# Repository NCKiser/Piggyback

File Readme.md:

Piggyback is a small circuit board that carries an Atmega-32u4-MU microprocessor and all of the supporting components needed for it to run. The only thing you need to provide is 5V power and ground.

Piggyback has 4 legs, each with 8 castellated holes spaced 0.1in (2.54mm) apart. These legs break out all of the GPIO, power, and USB Data pins. Each leg roughly corresponds to a port of the 32u4's IO.

Piggyback was designed with custom mechanical keyboard PCBs in mind. The board fits snuggly under a row of MX or Alps style switches spaced 0.75in (19.05mm) apart. The legs fit within the space between the switch footprints.

Piggyback features ESD protection on the USB data lines, as well as a 500mA resettable polyfuse on the 5V line.

To use the Piggyback in your PCB designs, (load and place the symbol and footprint in your schematic and PCB), and wire it up to your USB port and key matrix. If you are using a USB-C connector, you will need to take care of the CC pins on your own (usually with 5.1k resistors to ground).

PiggybackBT is based on the Kikoto bluetooth pro-micro board, source for that can be found here: https://github.com/zhiayang/mikoto

This is open-source, as long as you give credit, and is free for commercial use. You can make, modify, and sell this board as you please, as long as you do not claim to own the copyright.

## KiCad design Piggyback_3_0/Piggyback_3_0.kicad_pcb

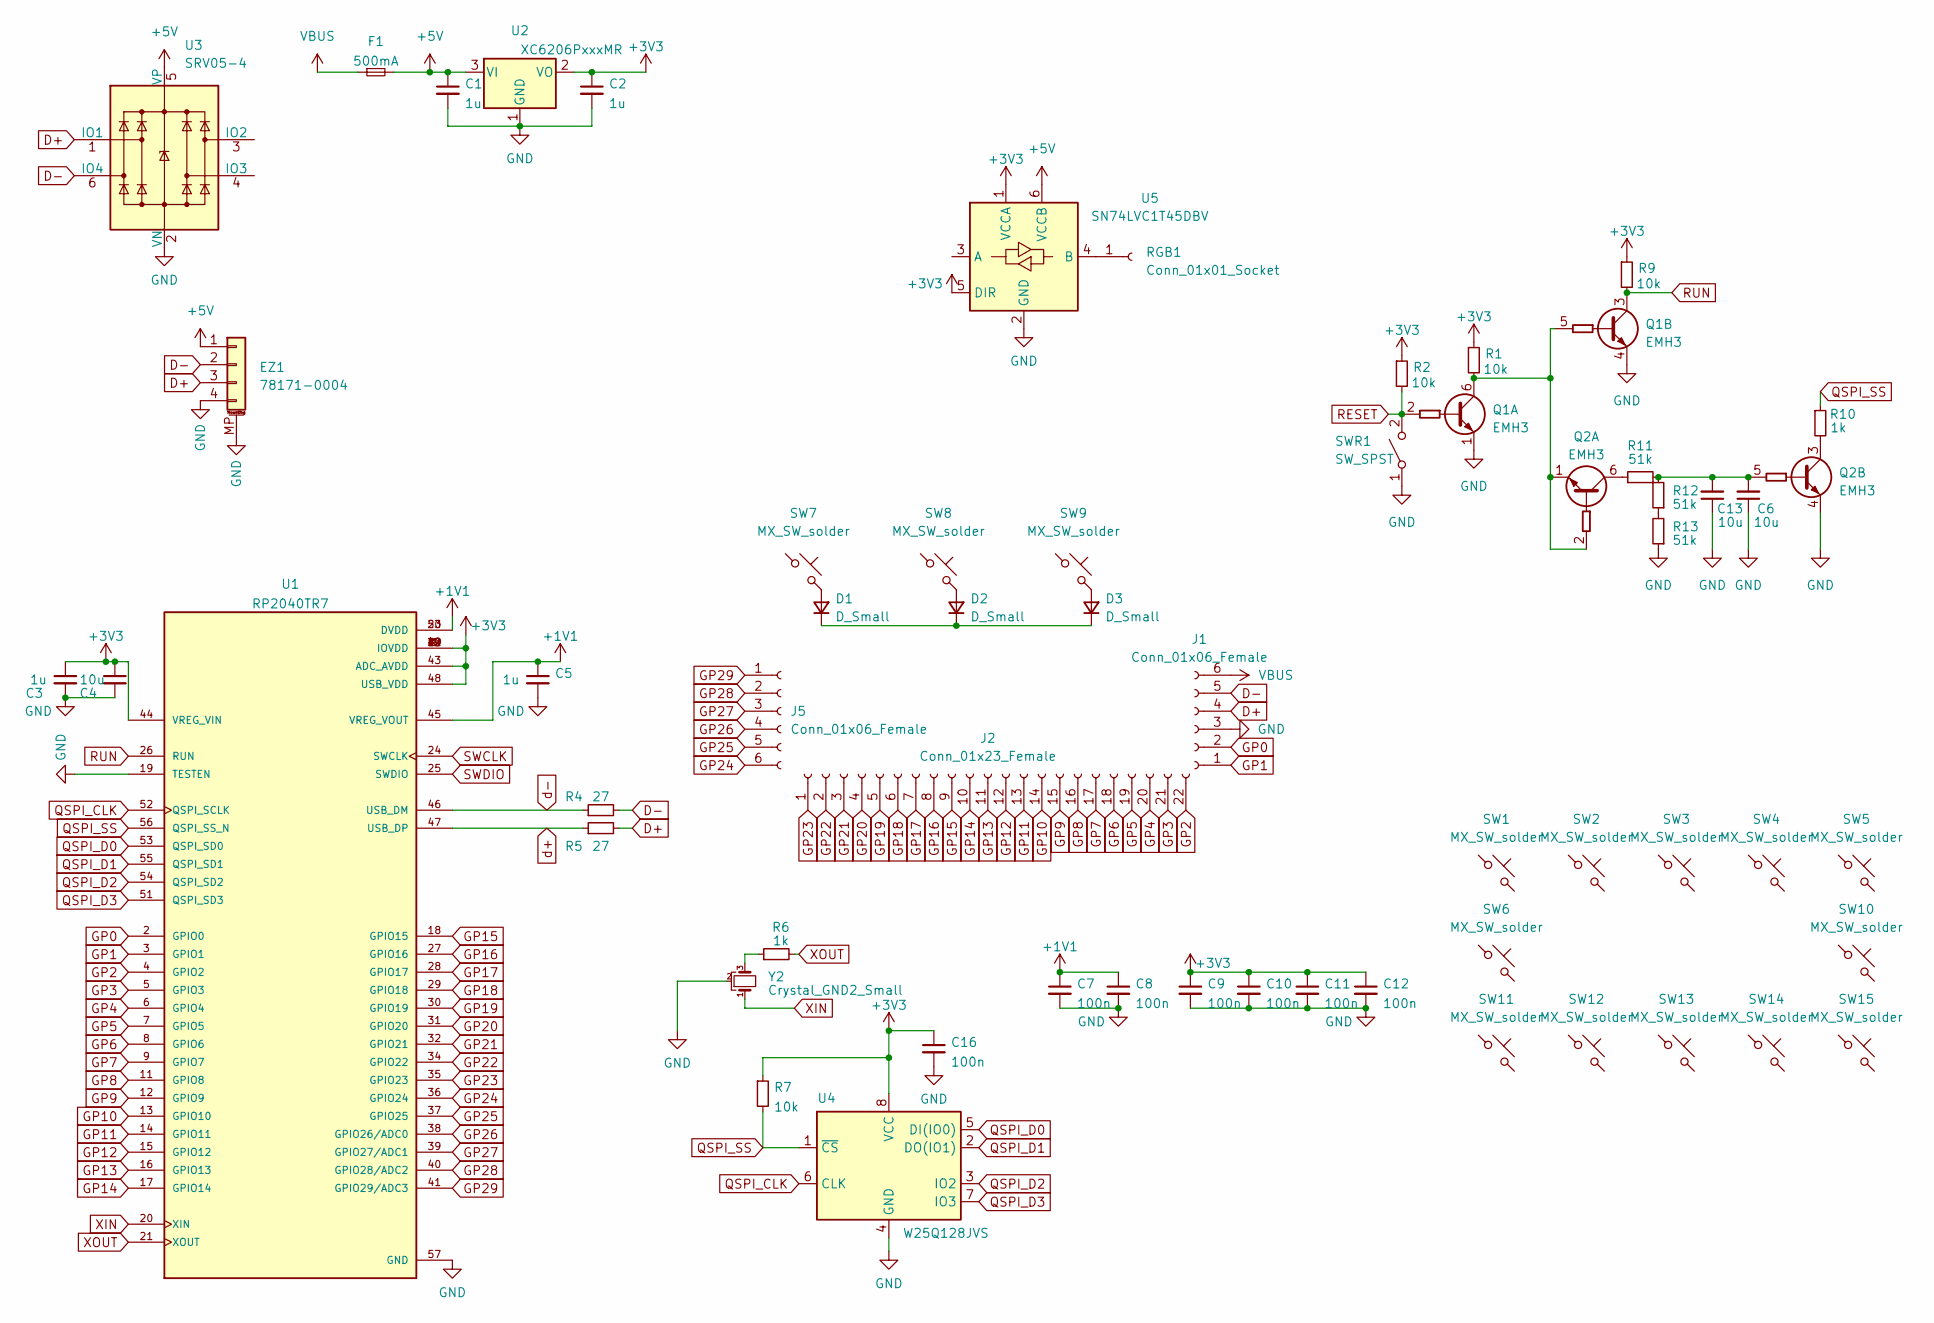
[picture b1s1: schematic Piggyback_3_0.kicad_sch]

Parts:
C1, C2, C3, C5: 1u; C_0402_1005Metric
C4, C6, C13: 10u; C_0402_1005Metric
C7, C8, C9, C10, C11, C12, C16: 100n; C_0402_1005Metric
D1, D2, D3: D_Small; D_SOD-123
EZ1: 78171-0004; PicoEZMate-Reinforced-Lite; Manufacturer Part Number 78171-0004; LCSC Part Number C588524
F1: 500mA; Fuse_1206_3216Metric
J1, J5: Conn_01x06_Female; PinHeader_1x06_P2.54mm_Vertical
J2: Conn_01x23_Female; PinHeader_1x22_P2.54mm_Vertical
Q1, Q2: EMH3; SOT-563
R1, R2, R7, R9: 10k; R_0402_1005Metric
R4, R5: 27; R_0402_1005Metric
R6, R10: 1k; R_0402_1005Metric
R11, R12, R13: 51k; R_0402_1005Metric
RGB1: Conn_01x01_Socket; PinSocket_1x01_P2.54mm_Vertical
SW1, SW2, SW3, SW4, SW5, SW6, SW7, SW8, SW9, SW10, SW11, SW12, SW13, SW14, SW15: MX_SW_solder; SW_MX_1u
SWR1: SW_SPST; SW_Push_SPST_NO_Alps_SKRK
U1: RP2040TR7; QFN40P700X700X90-57N; PARTREV 1.7.1
U2: XC6206PxxxMR; SOT-23
U3: SRV05-4; SOT-23-6-routable
U4: W25Q128JVS; SOIC-8_5.23x5.23mm_P1.27mm
U5: SN74LVC1T45DBV; SOT-23-6
Y2: Crystal_GND2_Small; Resonator_SMD_Murata_CSTxExxV-3Pin_3.0x1.1mm

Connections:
+1V1: C5.1, C7.1, C8.1, U1.23 (DVDD), U1.45 (VREG_VOUT), U1.50 (DVDD)
+3V3: C2.1, C3.1, C4.1, C9.1, C10.1, C11.1, C12.1, C16.1, R1.1, R2.1, R7.1, R9.1, U1.1 (IOVDD), U1.10 (IOVDD), U1.22 (IOVDD), U1.33 (IOVDD), U1.42 (IOVDD), U1.43 (ADC_AVDD), U1.44 (VREG_VIN), U1.48 (USB_VDD), U1.49 (IOVDD), U2.2 (VO), U4.8 (VCC), U5.1 (VCCA), U5.5 (DIR)
+5V: C1.1, EZ1.1, F1.2, U2.3 (VI), U3.5 (VP), U5.6 (VCCB)
D+: EZ1.3, J1.4, R5.2, U3.1 (IO1)
D-: EZ1.2, J1.5, R4.2, U3.6 (IO4)
GND: C1.2, C2.2, C3.2, C4.2, C5.2, C6.1, C7.2, C8.2, C9.2, C10.2, C11.2, C12.2, C13.1, C16.2, EZ1.4, EZ1.MP (MountPin), J1.3, Q1.1 (E1), Q1.4 (E2), Q2.4 (E2), R13.1, SWR1.1 (A), U1.19 (TESTEN), U1.57 (GND), U2.1 (GND), U3.2 (VN), U4.4 (GND), U5.2 (GND), Y2.2
GP0: J1.2, U1.2 (GPIO0)
GP1: J1.1, U1.3 (GPIO1)
GP2: J2.22, U1.4 (GPIO2)
GP3: J2.21, U1.5 (GPIO3)
GP4: J2.20, U1.6 (GPIO4)
GP5: J2.19, U1.7 (GPIO5)
GP6: J2.18, U1.8 (GPIO6)
GP7: J2.17, U1.9 (GPIO7)
GP8: J2.16, U1.11 (GPIO8)
GP9: J2.15, U1.12 (GPIO9)
GP10: J2.14, U1.13 (GPIO10)
GP11: J2.13, U1.14 (GPIO11)
GP12: J2.12, U1.15 (GPIO12)
GP13: J2.11, U1.16 (GPIO13)
GP14: J2.10, U1.17 (GPIO14)
GP15: J2.9, U1.18 (GPIO15)
GP16: J2.8, U1.27 (GPIO16)
GP17: J2.7, U1.28 (GPIO17)
GP18: J2.6, U1.29 (GPIO18)
GP19: J2.5, U1.30 (GPIO19)
GP20: J2.4, U1.31 (GPIO20)
GP21: J2.3, U1.32 (GPIO21)
GP22: J2.2, U1.34 (GPIO22)
GP23: J2.1, U1.35 (GPIO23)
GP24: J5.6, U1.36 (GPIO24)
GP25: J5.5, U1.37 (GPIO25)
GP26: J5.4, U1.38 (GPIO26/ADC0)
GP27: J5.3, U1.39 (GPIO27/ADC1)
GP28: J5.2, U1.40 (GPIO28/ADC2)
GP29: J5.1, U1.41 (GPIO29/ADC3)
unnamed: D1.2 (A), SW7.2
unnamed: D1.1 (K), D2.1 (K), D3.1 (K)
unnamed: D2.2 (A), SW8.2
unnamed: D3.2 (A), SW9.2
unnamed: Q1.5 (B2), Q1.6 (C1), Q2.1 (E1), Q2.2 (B1), R1.2
unnamed: Q2.6 (C1), R11.1
unnamed: C6.2, C13.2, Q2.5 (B2), R11.2, R12.2
unnamed: Q2.3 (C2), R10.2
unnamed: R6.1, Y2.3
unnamed: R12.1, R13.2
unnamed: RGB1.1, U5.4 (B)
QSPI_CLK: U1.52 (QSPI_SCLK), U4.6 (CLK)
QSPI_D0: U1.53 (QSPI_SD0), U4.5 (DI(IO0))
QSPI_D1: U1.55 (QSPI_SD1), U4.2 (DO(IO1))
QSPI_D2: U1.54 (QSPI_SD2), U4.3 (IO2)
QSPI_D3: U1.51 (QSPI_SD3), U4.7 (IO3)
QSPI_SS: R7.2, R10.1, U1.56 (QSPI_SS_N), U4.1 (~CS)
RESET: Q1.2 (B1), R2.2, SWR1.2 (B)
RUN: Q1.3 (C2), R9.2, U1.26 (RUN)
SWCLK: U1.24 (SWCLK)
SWDIO: U1.25 (SWDIO)
VBUS: F1.1, J1.6
XIN: U1.20 (XIN), Y2.1
XOUT: R6.2, U1.21 (XOUT)
d+: R5.1, U1.47 (USB_DP)
d-: R4.1, U1.46 (USB_DM)

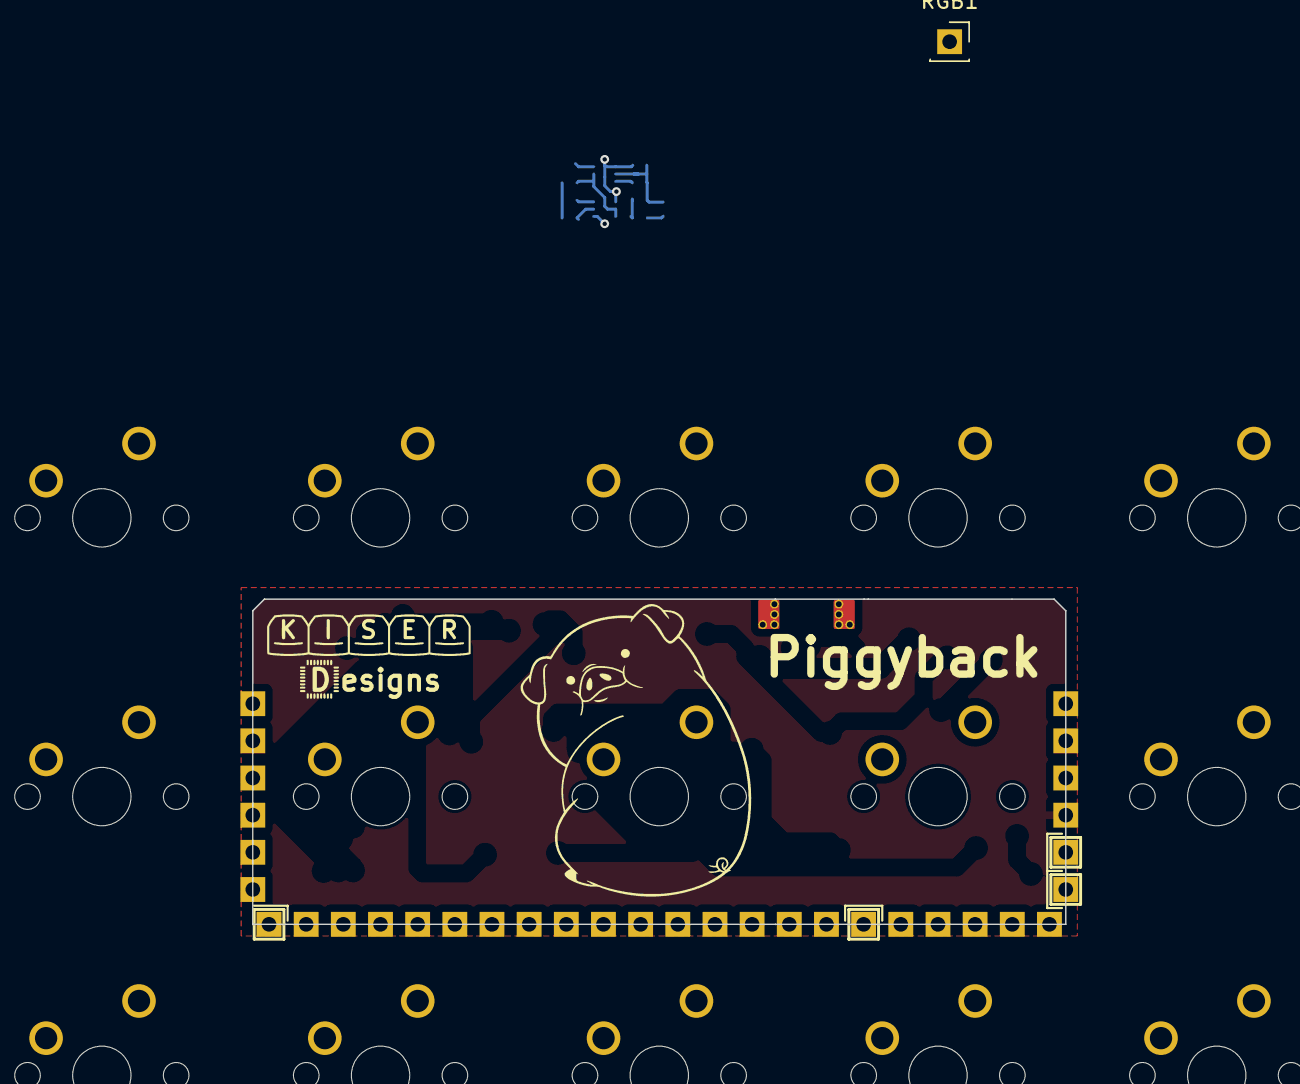
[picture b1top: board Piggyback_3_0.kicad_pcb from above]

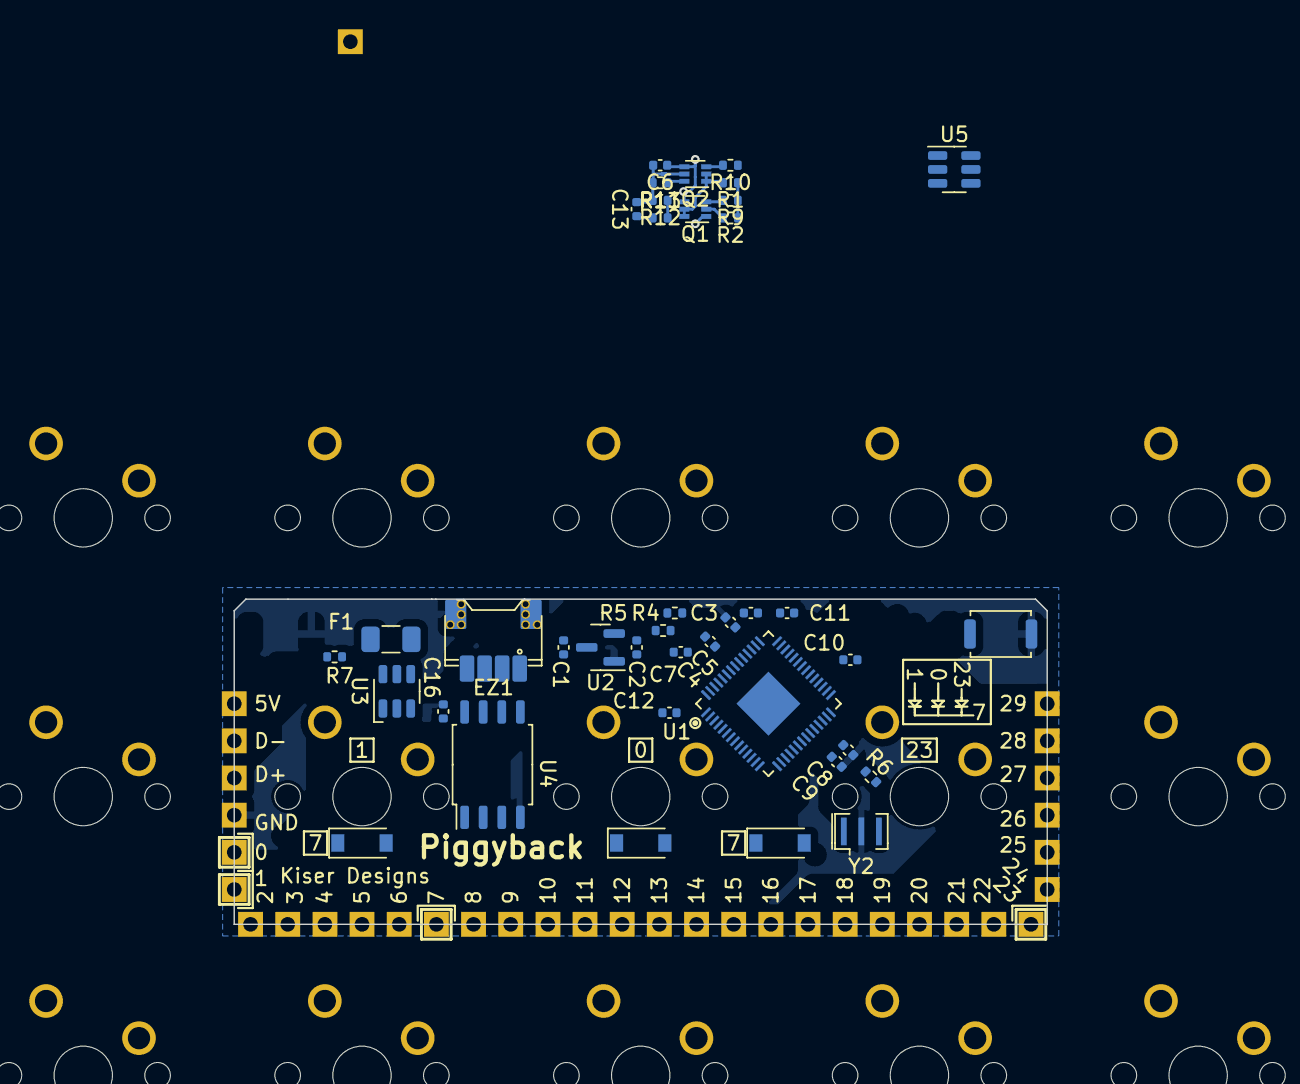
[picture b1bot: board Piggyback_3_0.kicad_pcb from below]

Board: 2 copper layers, 55.6 x 22.2 mm, 58 parts (40 on the bottom side), 60 nets.

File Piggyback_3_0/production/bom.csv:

Designator,Footprint,Quantity,Value,LCSC Part #
"C1, C2, C3, C5",0402,4,1u,
"C10, C11, C12, C16, C7, C8, C9",0402,7,100n,
C4,0402,1,10u,
"D1, D2, D3",D_SOD-123,3,D_Small,
EZ1,PicoEZMate-Reinforced-Lite,1,78171-0004,
F1,1206,1,500mA,
"J1, J5",PinHeader_1x06_P2.54mm_Vertical,2,Conn_01x06_Female,
J2,PinHeader_1x22_P2.54mm_Vertical,1,Conn_01x23_Female,
J3,USB_C_Receptacle_HRO_TYPE-C-31-M-12,1,USB_C_Receptacle_USB2.0,
"R1, R2, R3",0402,3,5.1k,
"R4, R5",0402,2,27,
"R6, R8",0402,2,1k,
R7,0402,1,-10k,
"SW7, SW8, SW9",SW_MX_1u,3,MX_SW_solder,
"SWR1, SWR2",SW_Push_SPST_NO_Alps_SKRK,2,SW_SPST,
U1,QFN40P700X700X90-57N,1,RP2040TR7,
U2,SOT-23,1,XC6206PxxxMR,
U3,SOT-23-6-routable,1,SRV05-4,
U4,SOIC-8_5.23x5.23mm_P1.27mm,1,W25Q128JVS,
Y2,Resonator_SMD_Murata_CSTxExxV-3Pin_3.0x1.1mm,1,Crystal_GND2_Small,

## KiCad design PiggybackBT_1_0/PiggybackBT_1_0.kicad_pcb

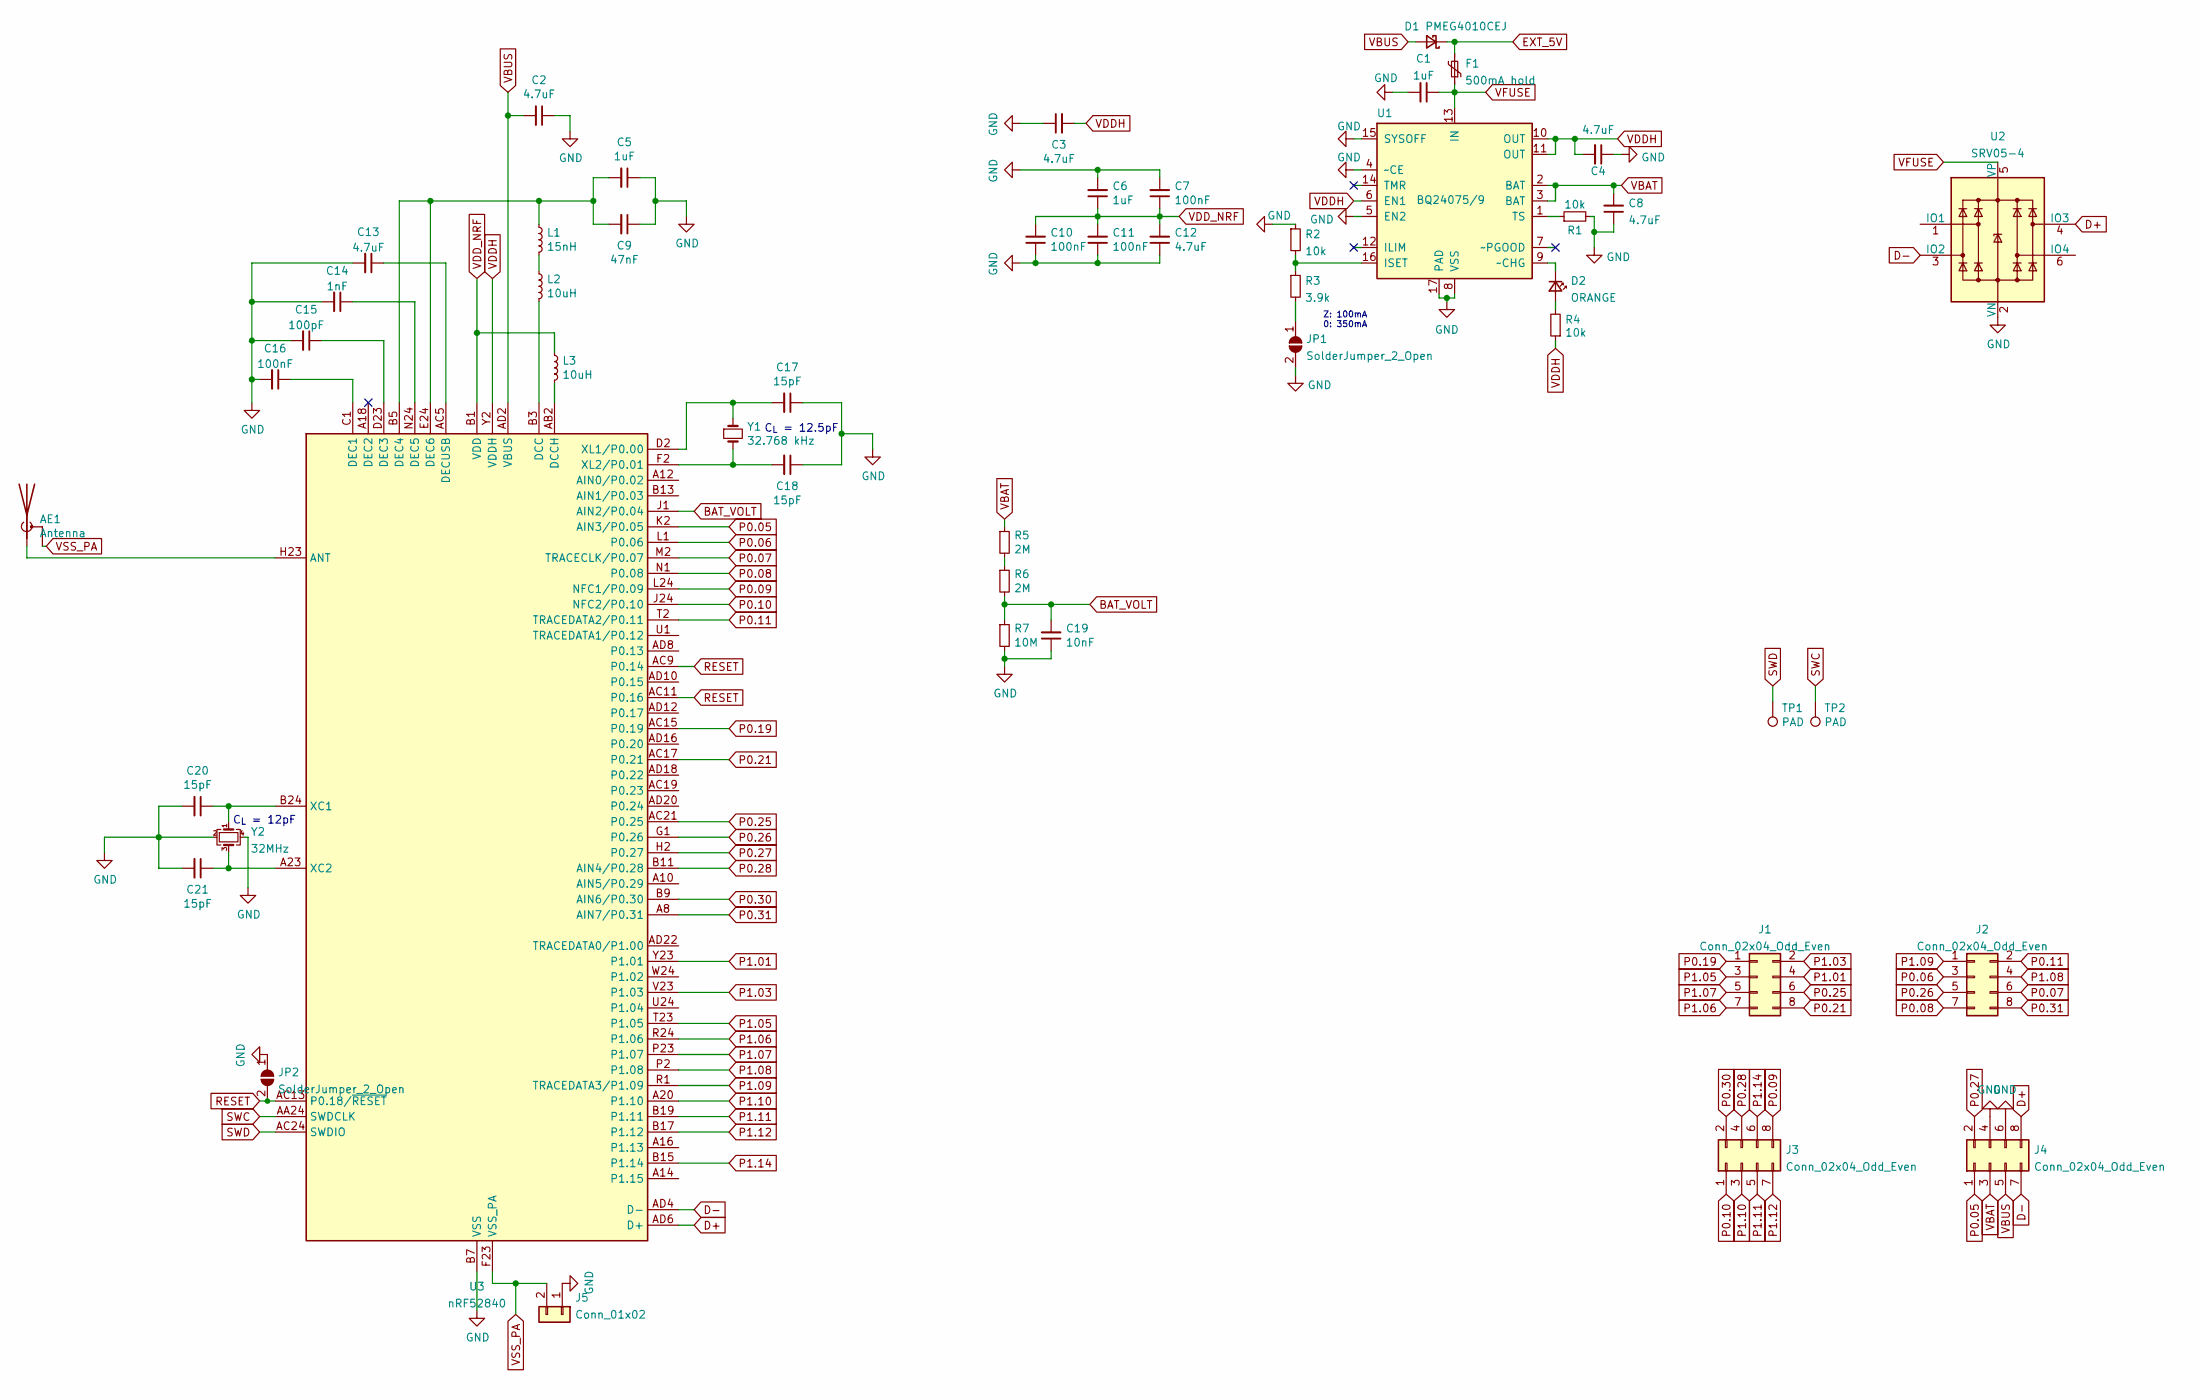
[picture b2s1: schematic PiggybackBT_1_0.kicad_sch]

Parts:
AE1: Antenna; U.FL_Hirose_U.FL-R-SMT-1_Vertical
C1, C5, C6: 1uF; C_0402_1005Metric; Manufacturer Part CL05A105KO5NNNC; LCSC Part C52923
C2, C3, C4, C8, C12, C13: 4.7uF; C_0402_1005Metric; Manufacturer Part CL05A475KP5NRNC; LCSC Part C368809
C7, C10, C11, C16: 100nF; C_0402_1005Metric; Manufacturer Part CL05B104KA5NNNC; LCSC Part C1525
C9: 47nF; C_0402_1005Metric; Manufacturer Part CL05B473KO5NNNC; LCSC Part C307434
C14: 1nF; C_0402_1005Metric; Manufacturer Part CL05B102KB5NNNC; LCSC Part C14442
C15: 100pF; C_0402_1005Metric; Manufacturer Part CL05C101JB5NNNC; LCSC Part C26409
C17, C18, C20, C21: 15pF; C_0402_1005Metric; Manufacturer Part CL05C150JB51PNC; LCSC Part C307341
C19: 10nF; C_0402_1005Metric; Manufacturer Part CL05B103KB5NNNC; LCSC Part C15195
D1: PMEG4010CEJ; D_SOD-323F; Manufacturer Part PMEG4010CEJ; LCSC Part C50704
D2: ORANGE; LED_0603_1608Metric; Manufacturer Part 19-217/S2C-AQ1R1B/3T; LCSC Part C160478
F1: 500mA hold; Fuse_0402_1005Metric; Manufacturer Part 0402L050SLKR; LCSC Part C206938
J1, J2, J3, J4: Conn_02x04_Odd_Even; PinHeader_2x04_P2.54mm_Vertical
J5: Conn_01x02; NetTie-2_SMD_Pad0.5mm
JP1, JP2: SolderJumper_2_Open; SolderJumper-2_P1.3mm_Open_RoundedPad1.0x1.5mm
L1: 15nH; L_0402_1005Metric; Manufacturer Part MLG1005S15NJT000; LCSC Part C76763
L2, L3: 10uH; L_0603_1608Metric; Manufacturer Part MLF1608E100KTD00; LCSC Part C76732
R1, R2, R4: 10k; R_0402_1005Metric; Manufacturer Part RC0402FR-0710KL; LCSC Part C60490
R3: 3.9k; R_0402_1005Metric; Manufacturer Part RC0402FR-073K9L; LCSC Part C131467
R5, R6: 2M; R_0402_1005Metric; Manufacturer Part RC0402FR-072ML; LCSC Part C138014
R7: 10M; R_0402_1005Metric; Manufacturer Part RC0402FR-0710ML; LCSC Part C138067
TP1, TP2: PAD; TestPoint_Pad_D1.0mm
U1: BQ24075/9; VQFN-16-1EP_3x3mm_P0.5mm_EP1.6x1.6mm; Manufacturer Part BQ24075RGTR; LCSC Part C15464
U2: SRV05-4; SOT-23-6
U3: nRF52840; Nordic_AQFN-73-1EP_7x7mm_P0.5mm
Y1: 32.768 kHz; Crystal_SMD_2012-2Pin_2.0x1.2mm; Manufacturer Part SC20S-12.5PF20PPM; LCSC Part C97607
Y2: 32MHz; Crystal_SMD_2016-4Pin_2.0x1.6mm; Manufacturer Part Q22FA1280001800; LCSC Part C255896

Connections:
BAT_VOLT: C19.2, R6.2, R7.1, U3.J1 (AIN2/P0.04)
D+: J4.8, U2.4 (IO3), U3.AD6 (D+)
D-: J4.7, U2.3 (IO2), U3.AD4 (D-)
EXT_5V: D1.1 (K), F1.2
GND: C1.2, C2.1, C3.1, C4.1, C5.1, C6.2, C7.2, C8.1, C9.1, C10.1, C11.1, C12.1, C13.2, C14.2, C15.2, C16.2, C17.1, C18.1, C19.1, C20.2, C21.2, J4.4, J4.6, J5.1, JP1.2 (B), JP2.1 (A), R1.2, R2.1, R7.2, U1.4 (~CE), U1.5 (EN2), U1.8 (VSS), U1.15 (SYSOFF), U1.17 (PAD), U2.2 (VN), U3.B7 (VSS), U3.EP (VSS), Y2.2, Y2.4
unnamed: AE1.1 (A), U3.H23 (ANT)
unnamed: C5.2, C9.2, L1.1, U3.B5 (DEC4), U3.E24 (DEC6)
unnamed: C13.1, U3.AC5 (DECUSB)
unnamed: C14.1, U3.N24 (DEC5)
unnamed: C15.1, U3.D23 (DEC3)
unnamed: C16.1, U3.C1 (DEC1)
unnamed: C17.2, U3.D2 (XL1/P0.00), Y1.1
unnamed: C18.2, U3.F2 (XL2/P0.01), Y1.2
unnamed: C20.1, U3.B24 (XC1), Y2.1
unnamed: C21.1, U3.A23 (XC2), Y2.3
unnamed: D2.1 (K), U1.9 (~CHG)
unnamed: D2.2 (A), R4.2
unnamed: JP1.1 (A), R3.2
unnamed: L1.2, L2.1
unnamed: L2.2, U3.B3 (DCC)
unnamed: L3.2, U3.AB2 (DCCH)
unnamed: R1.1, U1.1 (TS)
unnamed: R2.2, R3.1, U1.16 (ISET)
unnamed: R5.2, R6.1
P0.05: J4.1, U3.K2 (AIN3/P0.05)
P0.06: J2.3, U3.L1 (P0.06)
P0.07: J2.6, U3.M2 (TRACECLK/P0.07)
P0.08: J2.7, U3.N1 (P0.08)
P0.09: J3.8, U3.L24 (NFC1/P0.09)
P0.10: J3.1, U3.J24 (NFC2/P0.10)
P0.11: J2.2, U3.T2 (TRACEDATA2/P0.11)
P0.19: J1.1, U3.AC15 (P0.19)
P0.21: J1.8, U3.AC17 (P0.21)
P0.25: J1.6, U3.AC21 (P0.25)
P0.26: J2.5, U3.G1 (P0.26)
P0.27: J4.2, U3.H2 (P0.27)
P0.28: J3.4, U3.B11 (AIN4/P0.28)
P0.30: J3.2, U3.B9 (AIN6/P0.30)
P0.31: J2.8, U3.A8 (AIN7/P0.31)
P1.01: J1.4, U3.Y23 (P1.01)
P1.03: J1.2, U3.V23 (P1.03)
P1.05: J1.3, U3.T23 (P1.05)
P1.06: J1.7, U3.R24 (P1.06)
P1.07: J1.5, U3.P23 (P1.07)
P1.08: J2.4, U3.P2 (P1.08)
P1.09: J2.1, U3.R1 (TRACEDATA3/P1.09)
P1.10: J3.3, U3.A20 (P1.10)
P1.11: J3.5, U3.B19 (P1.11)
P1.12: J3.7, U3.B17 (P1.12)
P1.14: J3.6, U3.B15 (P1.14)
RESET: JP2.2 (B), U3.AC9 (P0.14), U3.AC11 (P0.16), U3.AC13 (P0.18/~RESET)
SWC: TP2.1, U3.AA24 (SWDCLK)
SWD: TP1.1, U3.AC24 (SWDIO)
VBAT: C8.2, J4.3, R5.1, U1.2 (BAT), U1.3 (BAT)
VBUS: C2.2, D1.2 (A), J4.5, U3.AD2 (VBUS)
VDDH: C3.2, C4.2, R4.1, U1.6 (EN1), U1.10 (OUT), U1.11 (OUT), U3.Y2 (VDDH)
VDD_NRF: C6.1, C7.1, C10.2, C11.2, C12.2, L3.1, U3.A22 (VDD), U3.AD14 (VDD), U3.AD23 (VDD), U3.B1 (VDD), U3.W1 (VDD)
VFUSE: C1.1, F1.1, U1.13 (IN), U2.5 (VP)
VSS_PA: AE1.2 (Shield), J5.2, U3.F23 (VSS_PA)

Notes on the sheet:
C_{L} = 12pF
C_{L} = 12.5pF
Z: 100mA 0: 350mA

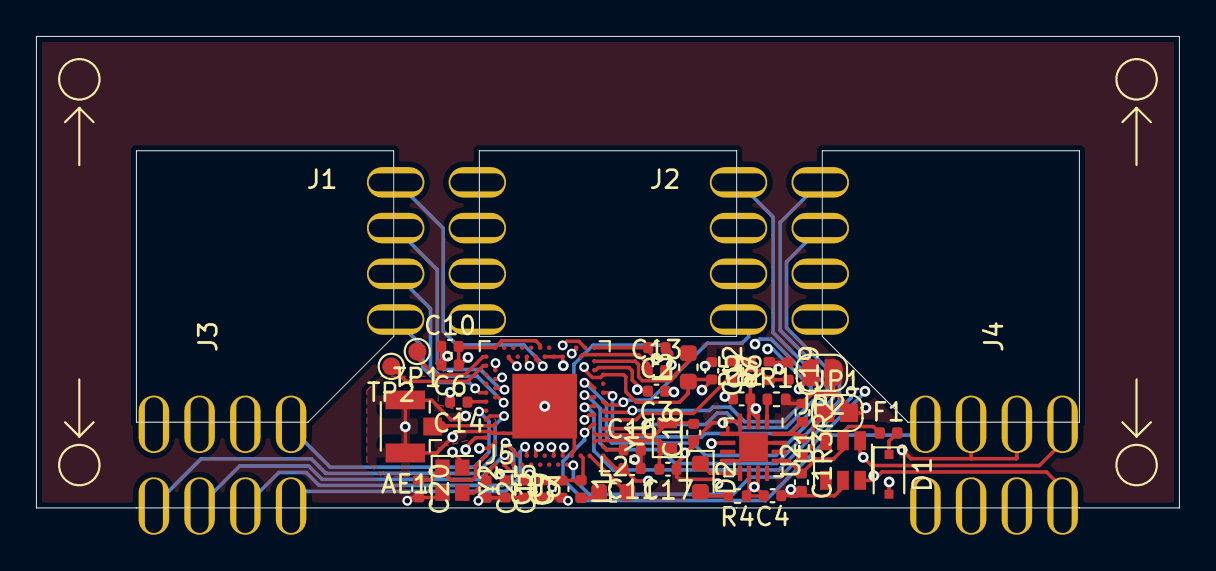
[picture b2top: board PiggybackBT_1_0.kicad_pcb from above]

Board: 4 copper layers, 63.5 x 26.2 mm, 49 parts (0 on the bottom side), 59 nets.

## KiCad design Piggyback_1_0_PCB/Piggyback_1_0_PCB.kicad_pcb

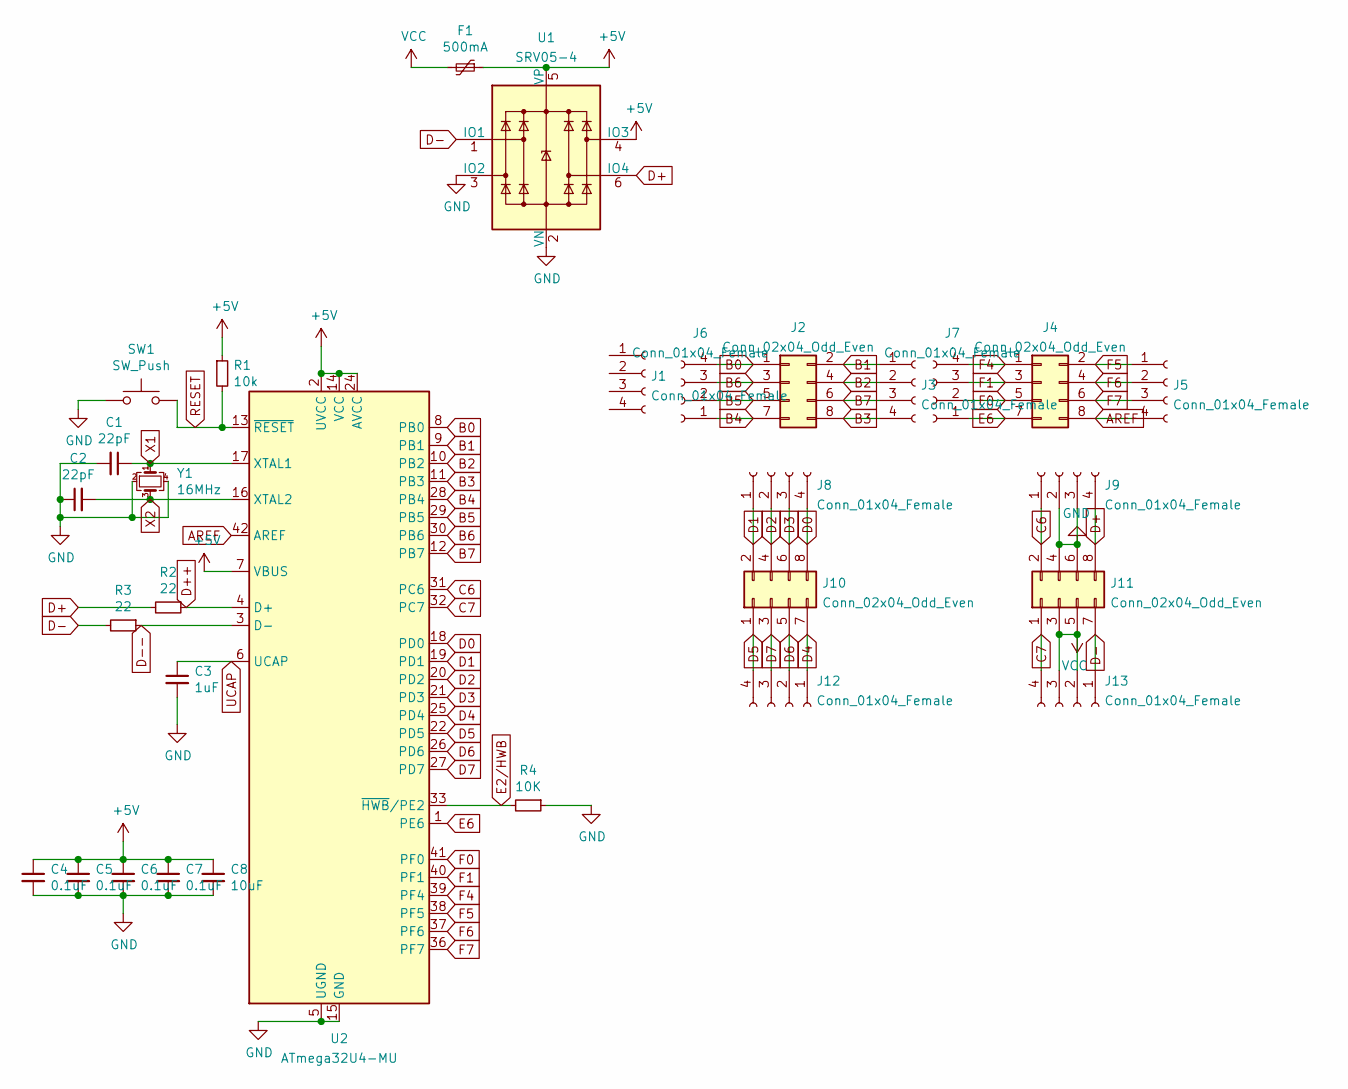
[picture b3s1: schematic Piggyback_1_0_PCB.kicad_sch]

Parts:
C1, C2: 22pF; C_0402_1005Metric
C3: 1uF; C_0402_1005Metric
C4, C5, C6, C7: 0.1uF; C_0402_1005Metric
C8: 10uF; C_0402_1005Metric
F1: 500mA; Fuse_1206_3216Metric
J1: Conn_01x04_Female
J2, J4, J10, J11: Conn_02x04_Odd_Even; PinHeader_2x04_P2.54mm_Vertical
J3, J5, J6, J7, J8, J9, J12, J13: Conn_01x04_Female; PinHeader_1x04_P2.54mm_Vertical
R1: 10k; R_0402_1005Metric
R2, R3: 22; R_0402_1005Metric
R4: 10K; R_0402_1005Metric
SW1: SW_Push; SW_SPST_PTS810
U1: SRV05-4; SOT-23-6
U2: ATmega32U4-MU; QFN-44-1EP_7x7mm_P0.5mm_EP5.2x5.2mm
Y1: 16MHz; Crystal_SMD_2520-4Pin_2.5x2.0mm

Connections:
+5V: C4.1, C5.1, C6.1, C7.1, C8.1, F1.1, R1.1, U1.4 (IO3), U1.5 (VP), U2.2 (UVCC), U2.7 (VBUS), U2.14 (VCC), U2.24 (AVCC), U2.34 (VCC), U2.44 (AVCC)
AREF: J4.8, J5.4, U2.42 (AREF)
B0: J2.1, J6.4, U2.8 (PB0)
B1: J2.2, J3.1, U2.9 (PB1)
B2: J2.4, J3.2, U2.10 (PB2)
B3: J2.8, J3.4, U2.11 (PB3)
B4: J2.7, J6.1, U2.28 (PB4)
B5: J2.5, J6.2, U2.29 (PB5)
B6: J2.3, J6.3, U2.30 (PB6)
B7: J2.6, J3.3, U2.12 (PB7)
C6: J9.1, J11.2, U2.31 (PC6)
C7: J11.1, J13.4, U2.32 (PC7)
D0: J8.4, J10.8, U2.18 (PD0)
D1: J8.1, J10.2, U2.19 (PD1)
D2: J8.2, J10.4, U2.20 (PD2)
D3: J8.3, J10.6, U2.21 (PD3)
D4: J10.7, J12.1, U2.25 (PD4)
D5: J10.1, J12.4, U2.22 (PD5)
D6: J10.5, J12.2, U2.26 (PD6)
D7: J10.3, J12.3, U2.27 (PD7)
D+: J9.4, J11.8, R2.2, U1.6 (IO4)
D++: R2.1, U2.4 (D+)
D-: J11.7, J13.1, R3.2, U1.1 (IO1)
D--: R3.1, U2.3 (D-)
E2/HWB: R4.2, U2.33 (~HWB/PE2)
E6: J4.7, J7.1, U2.1 (PE6)
F0: J4.5, J7.2, U2.41 (PF0)
F1: J4.3, J7.3, U2.40 (PF1)
F4: J4.1, J7.4, U2.39 (PF4)
F5: J4.2, J5.1, U2.38 (PF5)
F6: J4.4, J5.2, U2.37 (PF6)
F7: J4.6, J5.3, U2.36 (PF7)
GND: C1.2, C2.1, C3.2, C4.2, C5.2, C6.2, C7.2, C8.2, J9.2, J9.3, J11.4, J11.6, R4.1, SW1.1, U1.2 (VN), U1.3 (IO2), U2.5 (UGND), U2.15 (GND), U2.23 (GND), U2.35 (GND), U2.43 (GND), U2.45 (GND), Y1.2, Y1.4
RESET: R1.2, SW1.2, U2.13 (~RESET)
UCAP: C3.1, U2.6 (UCAP)
VCC: F1.2, J11.3, J11.5, J13.2, J13.3
X1: C1.1, U2.17 (XTAL1), Y1.1
X2: C2.2, U2.16 (XTAL2), Y1.3

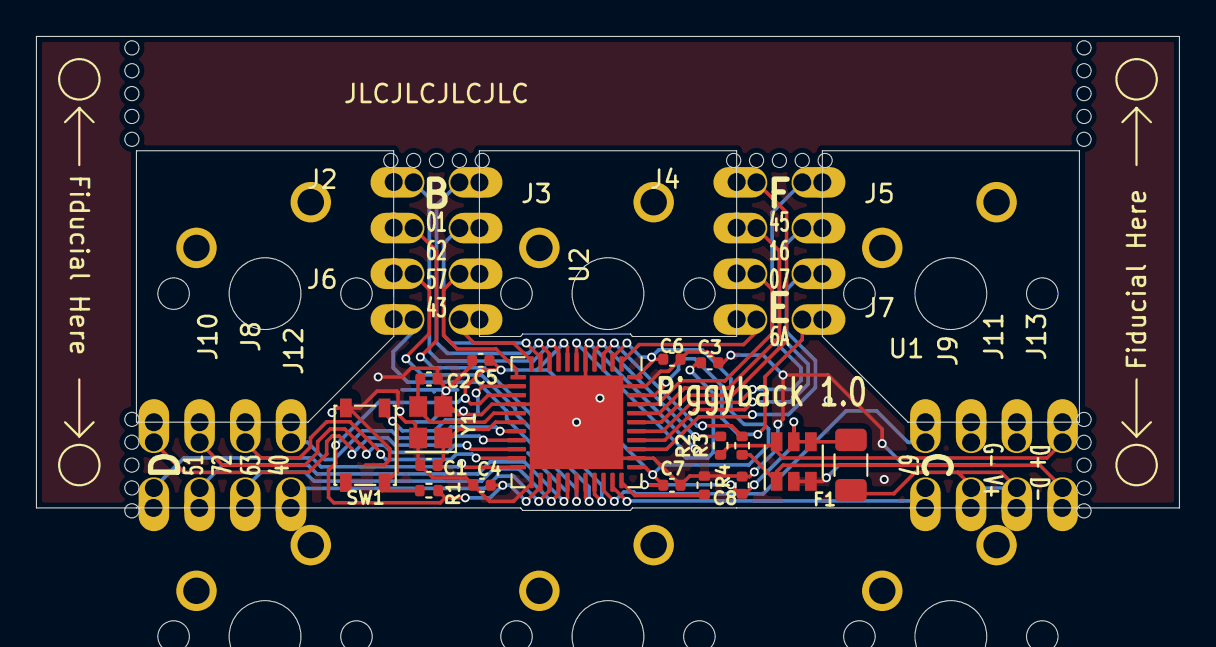
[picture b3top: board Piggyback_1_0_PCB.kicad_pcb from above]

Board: 2 copper layers, 63.5 x 26.3 mm, 29 parts (0 on the bottom side), 38 nets.

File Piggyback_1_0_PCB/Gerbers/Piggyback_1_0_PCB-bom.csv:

Designator,Footprint,Value,Tolerance,MFG Part #,Can replace with other similar parts?
Y1,Y_2520-4Pin_2.5x2.0mm,16MHz,,7E16000E09UCG,Maybe
C8,C_0402_1005Metric,10uF,10%,GRM155R61A106ME44D,Yes
"C1,C2",C_0402_1005Metric,22pF,10%,0402CG220J500NT,Yes
"C4,C5,C6,C7",C_0402_1005Metric,0.1uF,10%,CL05B104KO5NNNC,Yes
C3,C_0402_1005Metric,1uF,10%,CL05A105KA5NQNC,Yes
"R1,R4",R_0402_1005Metric,10k,10%,0402WGF1002TCE,Yes
SW1,SW_SPST_PTS810,,,PTS810SJM250SMTRLFS,No
F1,F_1206_3216Metric,500mA,,nSMD050-24V,No
"R3,R2",R_0402_1005Metric,22 ohm,10%,0402WGF220JTCE,Yes
U1,SOT-23-6,,,SRV05-4-P-T7,No
U2,QFN-44-1EP_7x7mm_P0.5mm_EP5.2x5.2mm,Atmel-DFU Bootloader,,ATmega32U4-MU,No

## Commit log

2021-10-21 1.0 commit
2021-10-21 Public commit
2021-10-21 1.0 Pic
2021-10-21 Picture in Readme
2021-10-21 Connected NC pads to GND and 5V
2021-10-21 More material around edge vias, no longer "castellated"
2021-10-21 loose ends
2021-10-21 reset button clearance
2021-10-21 smaller crystal
2021-10-22 Changes for FAB
2021-10-24 created KiCad symbol and footprints for 1.0
2021-10-31 Manu for 43u5 version, added BT variant
2022-04-13 Minor Updates
2023-03-08 maybe?
2023-03-15 made a lot of changes
2023-03-18 add gerbers
2023-03-19 cost engineering
2023-03-19 further cost reductions
2023-03-20 usb-spec crystal
2023-03-25 add 3d model, and footprint
2023-04-07 add untested footprint .zip
2023-04-24 backups
2023-04-27 add piggyback 3
